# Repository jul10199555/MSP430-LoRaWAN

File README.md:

# MSP430-LoRaWAN
Integration of LoRaWAN using MSP430FR59XXLP Microcontrollers
-------

The goal of this repo is to optimize the code of a LoRaWAN wireless sensor node to achieve a lower power consumption, regulate LoRa TX / RX power, 
to add bidirectional (Uplink & acknowledge/downlink) communication capabilities on gateway & sensor node and the integration of pH, conductivity, temperature, 
humidity and atmospheric pressure sensors.

Previous work posted in by Daniel Ayala <br />
https://github.com/danielayala80/Energia-LMIC-library 

A fork from original source: <br />
https://github.com/DeuxVis/energia-lmic

Both clones of the original arduino repo: <br />
https://github.com/matthijskooijman/arduino-lmic

Check out also the TheThingsNetwork Library <br />
https://github.com/TheThingsNetwork/arduino-device-lib

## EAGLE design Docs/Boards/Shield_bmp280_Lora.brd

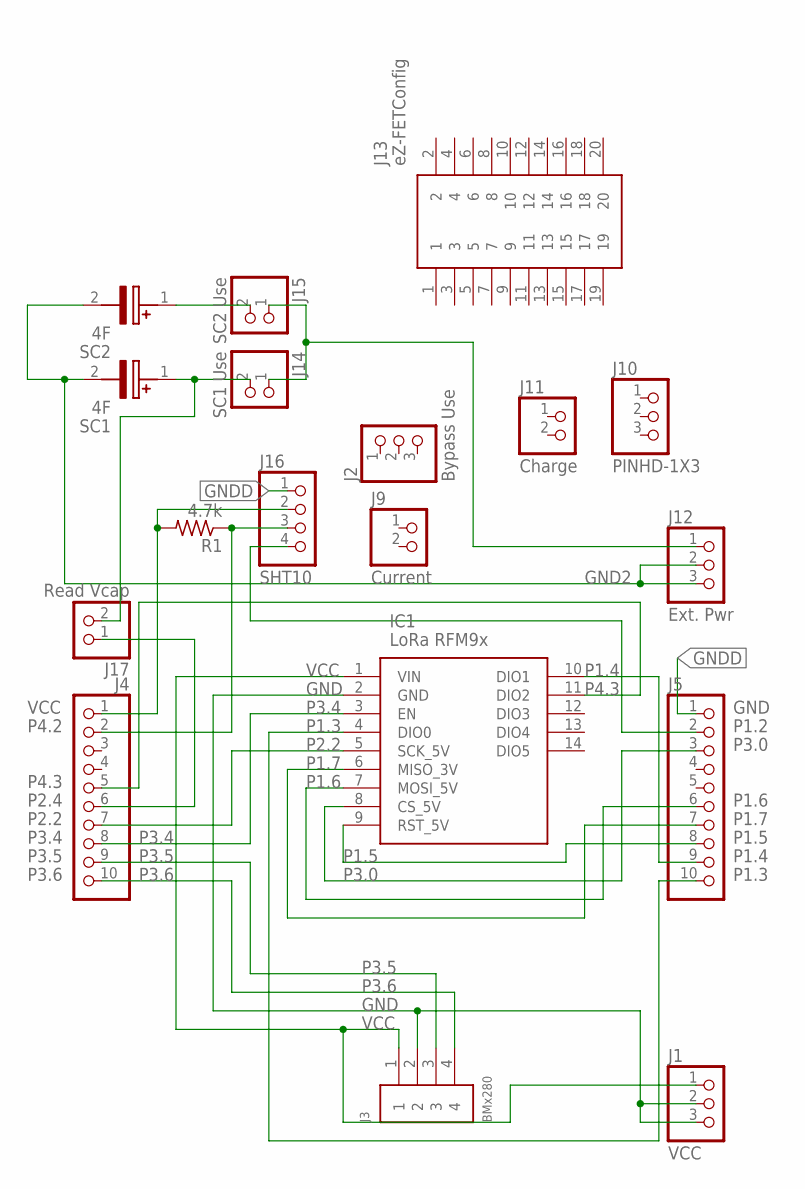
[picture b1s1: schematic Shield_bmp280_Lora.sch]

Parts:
IC1: LoRa RFM9x; 3072
J1: VCC; 1X03
J2: Bypass Use; 1X03
J3: BMx280; 61300411121
J4: VCC; 1X10-BIG
J5: GND; 1X10-BIG
J9: Current; 1X02
J10: PINHD-1X3; 1X03
J11: Charge; 1X02
J12: Ext. Pwr; 1X03
J13: eZ-FETConfig; HWS1881
J14: SC1 Use; 1X02
J15: SC2 Use; 1X02
J16: SHT10; 1X04
J17: Read Vcap; 1X02
R1: 4.7k; 0204/7
SC1, SC2: 4F; EECRG0V105VN

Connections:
GND: IC1.2 (GND), J1.2, J1.3, J3.2
GND2: J12.2, J12.3, SC1.2 (-), SC2.2 (-)
GNDD: J5.1, J16.1
unnamed: J14.2, J17.2, SC1.1 (+)
unnamed: J15.2, SC2.1 (+)
P1.2: J5.2, J16.4
P1.3: IC1.4 (DIO0), J5.10
P1.4: IC1.10 (DIO1), J5.9
P1.5: IC1.9 (RST_5V), J5.8
P1.6: IC1.7 (MOSI_5V), J5.6
P1.7: IC1.6 (MISO_3V), J5.7
P2.2: IC1.5 (SCK_5V), J4.7
P2.4: J4.6, J17.1
P3.0: IC1.8 (CS_5V), J5.3
P3.4: IC1.3 (EN), J4.8
P3.5: J3.3, J4.9
P3.6: J3.4, J4.10
P4.2: J4.2, J16.3, R1.1
P4.3: IC1.11 (DIO2), J4.5
VCC: IC1.1 (VIN), J1.1, J3.1
VCCA: J4.1, J16.2, R1.2
VCCC: J12.1, J14.1, J15.1

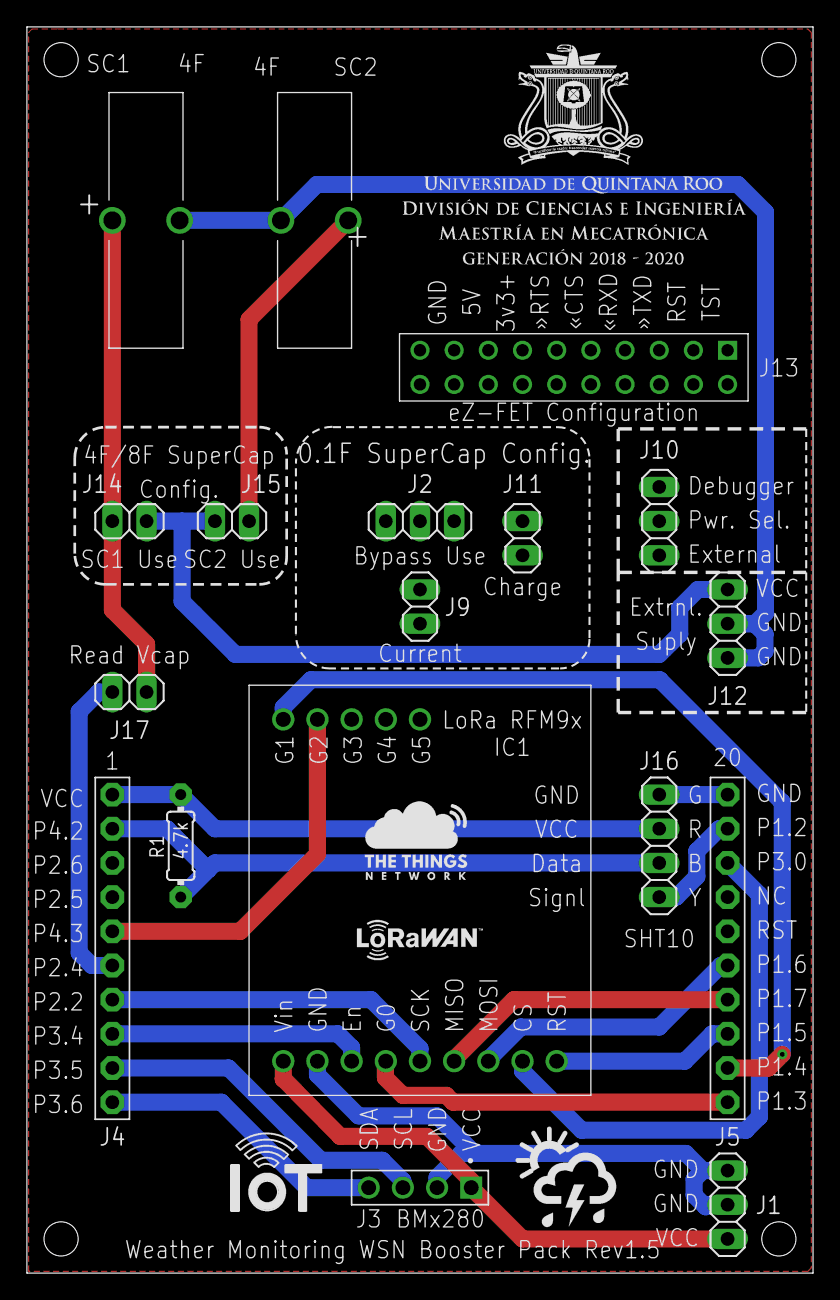
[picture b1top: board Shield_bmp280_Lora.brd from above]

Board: 2 copper layers, 58.4 x 92.6 mm, 18 parts (0 on the bottom side), 22 nets.

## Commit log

2022-11-07 Reestructuracion
2022-11-07 Agregando gateways lora
2022-11-07 Estructura
2022-11-07 Librerias de sensores
2022-11-07 programa con otros sensores
2022-11-07 Version 2 del nodo con sensor bmp280
2022-11-07 correction
2022-11-07 Especificando el entorno
2022-11-07 update source
2022-11-07 Info sensores
2022-11-12 update main
2022-11-12 info updated
2022-11-16 update description
2023-02-10 tarjetas MSP430FR5969
